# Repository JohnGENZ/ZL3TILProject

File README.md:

# ZL3TILProject

This repository contains support files for two presentations made to the Marlborough NZART in July and August 2019.

The presentations covered the tools and methods used to layout printed circuit boards with an emphasis on using SMD components, followed by ways of manufacturing a board, and finally the assembly of a board.

The example used to illustrate the topic is the function generator described in this blog article. http://www.technoblogy.com/show?2FCL 

The first files to refer to are the speaking notes pt1 and 2.  These are the notes for the presentation.  They are not intended to be a tutorial, but rather a curated  set of links to the excellent online resources available for the topic.

Included in the repository are copies of the parts libraries provided by Adafruit and Sparkfun.  These were included for convenience during the presentation.  You are best advised to download up to date copies from these companies’ websites, and also the Seeed open parts library from the Seeed website.

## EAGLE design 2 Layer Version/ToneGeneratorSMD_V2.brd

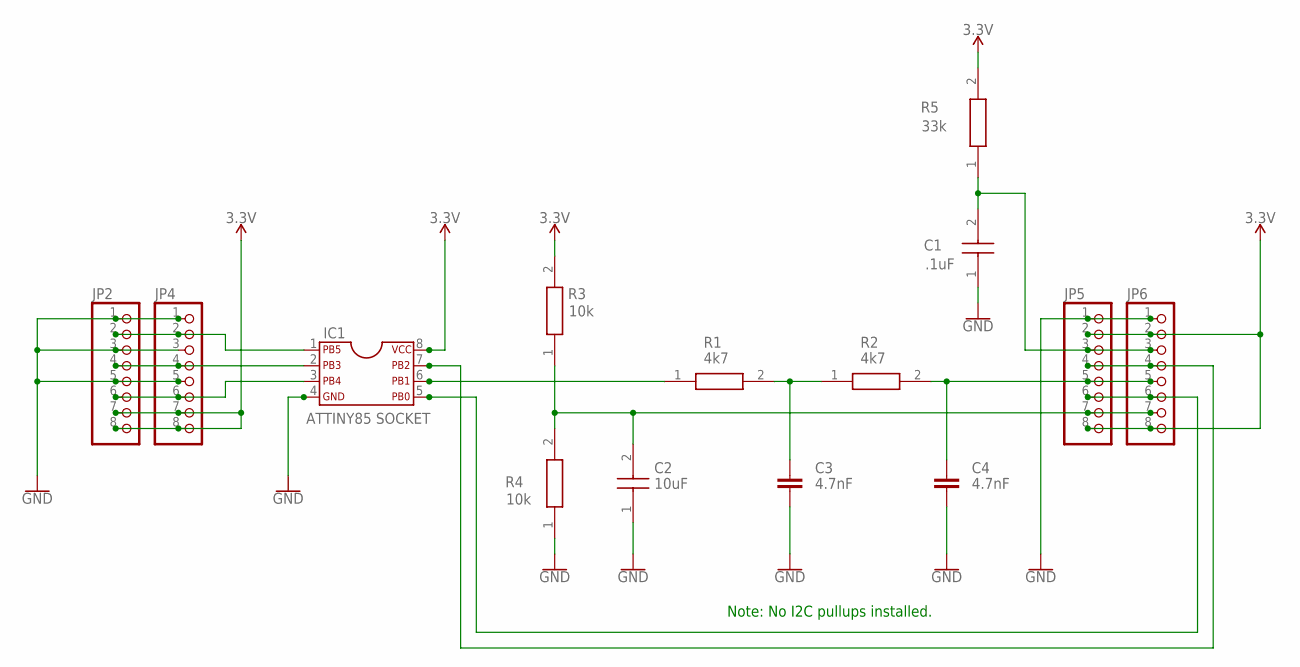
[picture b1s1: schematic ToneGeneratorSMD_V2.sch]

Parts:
C1: .1uF; CAPC2012X90N
C2: 10uF; CAPC2012X145N
C3, C4: 4.7nF; C0805
IC1: ATTINY85 SOCKET; DIL08ATTINY85
JP2, JP4, JP5, JP6: PINHD-1X8; 1X08
R1, R2: 4k7; RESC2013X65N
R3, R4: 10k; RESC2013X65N
R5: 33k; RESC2013X65N

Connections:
3.3V: IC1.8, JP2.7, JP2.8, JP4.7, JP4.8, JP5.2, JP5.8, JP6.2, JP6.8, R3.2 (R2), R5.2 (R2)
GND: C1.1, C2.1, C3.2, C4.2, IC1.4, JP2.1, JP2.3, JP2.5, JP4.1, JP4.3, JP4.5, JP5.1, JP6.1, R4.1 (R1)
unnamed: C3.1, R1.2 (R2), R2.1 (R1)
unnamed: C4.1, JP5.5, JP6.5, R2.2 (R2)
unnamed: IC1.6, R1.1 (R1)
unnamed: IC1.7, JP5.4, JP6.4
unnamed: IC1.1, JP2.2, JP4.2
unnamed: IC1.2, JP2.4, JP4.4
unnamed: IC1.3, JP2.6, JP4.6
unnamed: C1.2, JP5.3, JP6.3, R5.1 (R1)
unnamed: IC1.5, JP5.6, JP6.6
unnamed: C2.2, JP5.7, JP6.7, R3.1 (R1), R4.2 (R2)

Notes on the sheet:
Note: No I2C pullups installed.

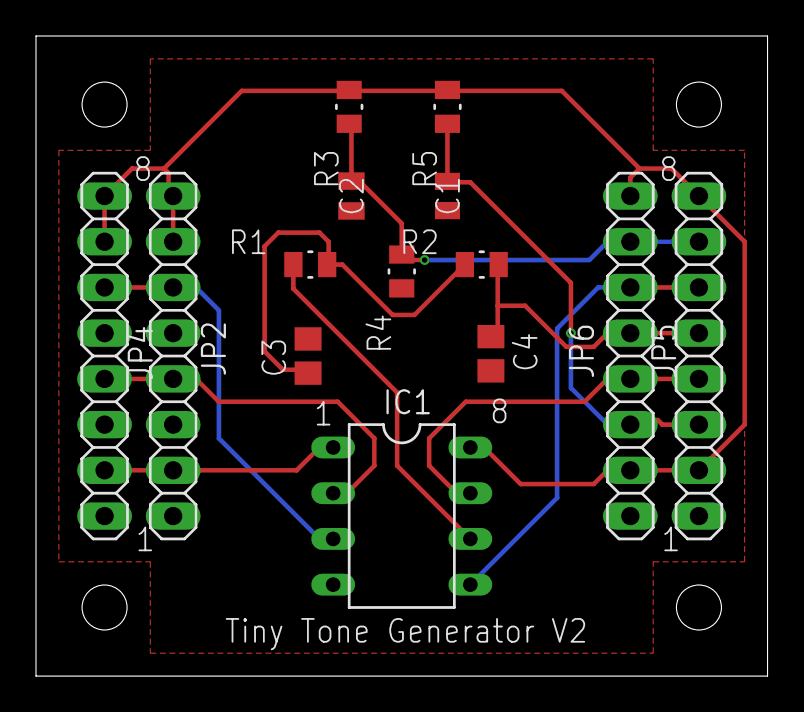
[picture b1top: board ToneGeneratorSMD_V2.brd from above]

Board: 4 copper layers, 40.6 x 35.6 mm, 14 parts (0 on the bottom side), 12 nets.

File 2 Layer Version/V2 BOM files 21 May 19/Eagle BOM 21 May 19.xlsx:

Qty | Value | Device | Package | Parts | Description | DESCRIPTION.1 | HEIGHT | MANUFACTURER_NAME | MANUFACTURER_PART_NUMBER | MOUSER_PART_NUMBER | MOUSER_PRICE-STOCK | SPICEPREFIX | Column1
1 | .1uF | 885012207098 | CAPC2012X90N | C1 | Multilayer Ceramic Capacitors MLCC - SMD/SMT WCAP-CSGP 0.1uF 0805 10% 50V MLCC | Multilayer Ceramic Capacitors MLCC - SMD/SMT WCAP-CSGP 0.1uF 0805 10% 50V MLCC | 0.9mm | Wurth Elektronik | 885012207098 | 710-885012207098 | https://www.mouser.com/Search/Refine.aspx?Keyword=710-885012207098
2 | 10k | ERJ-6GEYJ472V | RESC2013X65N | R3, R4 | RESISTOR, 0805 4.7K Ohm +/-5% 0.125 W | RESISTOR, 0805 4.7K Ohm +/-5% 0.125 W | mm | Panasonic | ERJ-6GEYJ472V | 667-ERJ-6GEYJ472V | https://www.mouser.com/Search/Refine.aspx?Keyword=667-ERJ-6GEYJ472V
1 | 10uF | GRM21BR61E106MA73L | CAPC2012X145N | C2 | Multilayer Ceramic Capacitors MLCC - SMD/SMT 0805 10uF 25volts X5R 20% | Multilayer Ceramic Capacitors MLCC - SMD/SMT 0805 10uF 25volts X5R 20% | 1.45mm | Murata Electronics | GRM21BR61E106MA73L | 81-GRM21BR61E106MA3L | https://www.mouser.com/Search/Refine.aspx?Keyword=81-GRM21BR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
1 | 33k | ERJ-6GEYJ472V | RESC2013X65N | R5 | RESISTOR, 0805 4.7K Ohm +/-5% 0.125 W | RESISTOR, 0805 4.7K Ohm +/-5% 0.125 W | mm | Panasonic | ERJ-6GEYJ472V | 667-ERJ-6GEYJ472V | https://www.mouser.com/Search/Refine.aspx?Keyword=667-ERJ-6GEYJ472V
2 | 4.7nF | C-EUC0805 | C0805 | C3, C4 | CAPACITOR, European symbol |  |  |  |  |  |  | C
2 | 4k7 | ERJ-6GEYJ472V | RESC2013X65N | R1, R2 | RESISTOR, 0805 4.7K Ohm +/-5% 0.125 W | RESISTOR, 0805 4.7K Ohm +/-5% 0.125 W | mm | Panasonic | ERJ-6GEYJ472V | 667-ERJ-6GEYJ472V | https://www.mouser.com/Search/Refine.aspx?Keyword=667-ERJ-6GEYJ472V

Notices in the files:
parts and their libraries:
SparkFun-PowerSymbols: Licensing: Creative Commons ShareAlike 4.0 International - https://creativecommons.org/licenses/by-sa/4.0
